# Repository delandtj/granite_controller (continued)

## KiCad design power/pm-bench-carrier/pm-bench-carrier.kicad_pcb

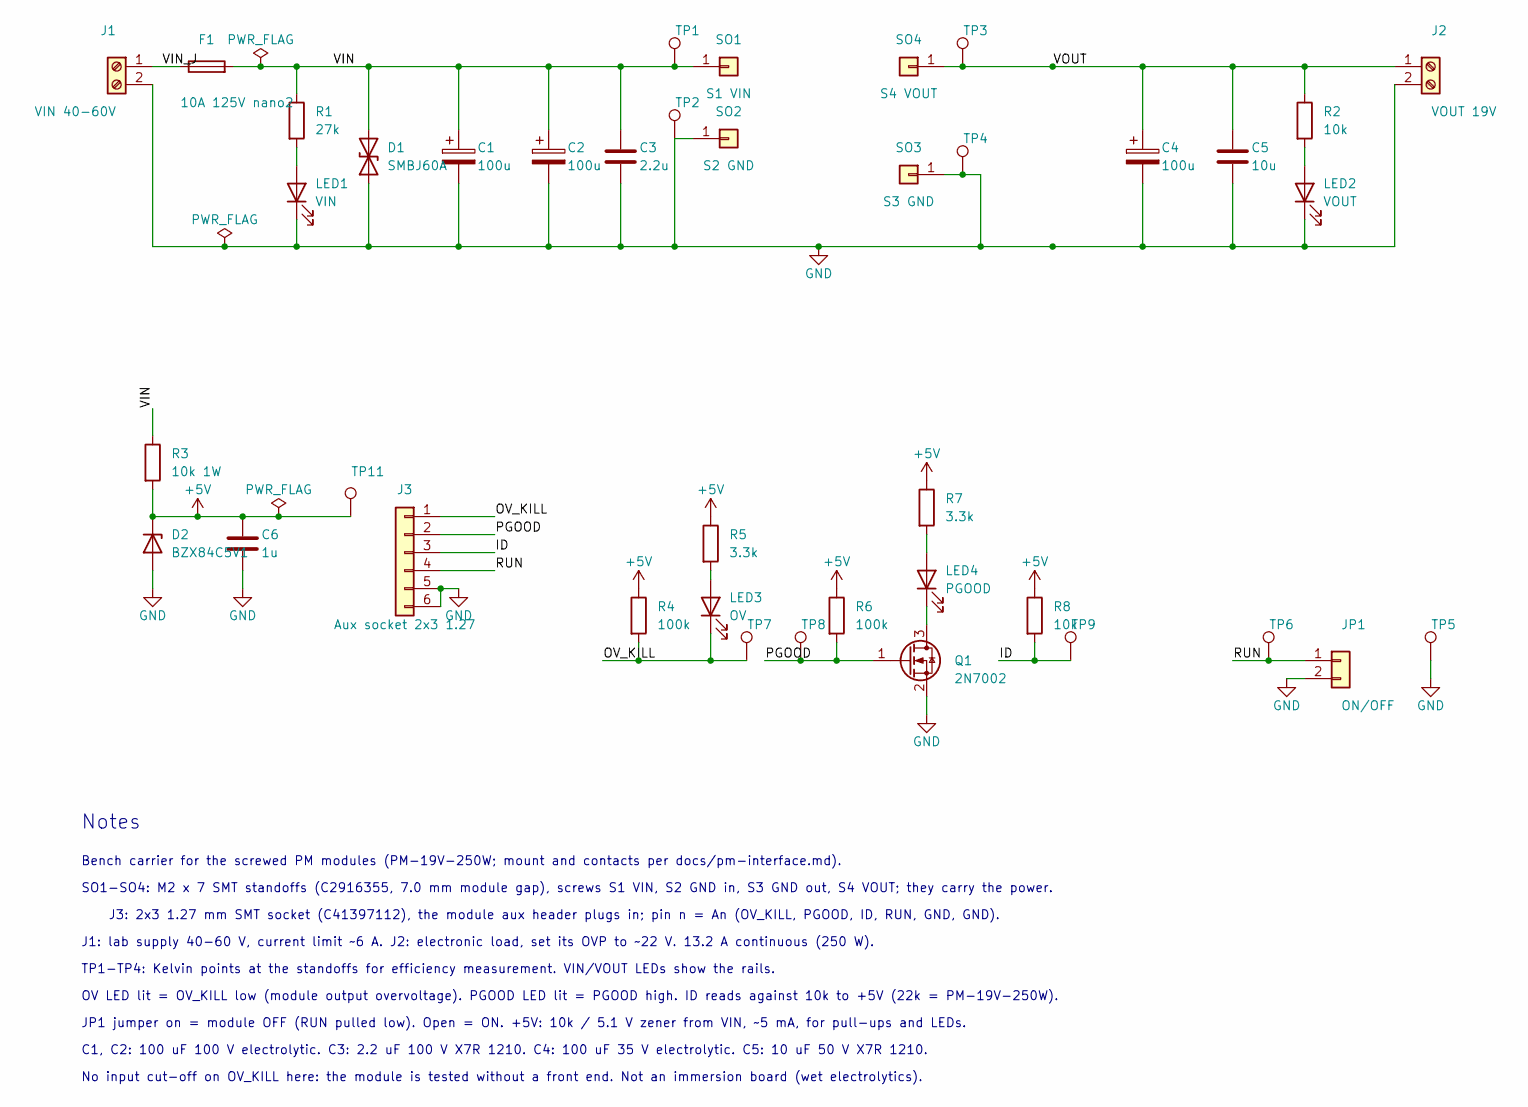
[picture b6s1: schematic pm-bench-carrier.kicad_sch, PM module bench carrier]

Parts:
C1, C2: 100u; CP_Radial_D10.0mm_P5.00mm
C3: 2.2u; C_1210_3225Metric; LCSC C55151
C4: 100u; CP_Radial_D8.0mm_P3.50mm
C5: 10u; C_1210_3225Metric; LCSC C2918502
C6: 1u; C_0603_1608Metric; LCSC C15849
D1: SMBJ60A; D_SMB; LCSC C353345
D2: BZX84C5V1; SOT-23; LCSC C27131
F1: 10A 125V nano2; Fuse_Littelfuse-NANO2-451_453; LCSC C44479
J1: VIN 40-60V; TerminalBlock_Phoenix_MKDS-3-2-5.08_1x02_P5.08mm_Horizontal
J2: VOUT 19V; TerminalBlock_Phoenix_MKDS-3-2-5.08_1x02_P5.08mm_Horizontal
J3: Aux socket 2x3 1.27; PM_Aux_Socket_2x03_P1.27; LCSC C41397112
JP1: ON/OFF; PinHeader_1x02_P2.54mm_Vertical
LED1: VIN; LED_0805_2012Metric; LCSC C2297
LED2: VOUT; LED_0805_2012Metric; LCSC C2297
LED3: OV; LED_0805_2012Metric; LCSC C84256
LED4: PGOOD; LED_0805_2012Metric; LCSC C2297
Q1: 2N7002; SOT-23; LCSC C8545
R1: 27k; R_1206_3216Metric; LCSC C17943
R2: 10k; R_0805_2012Metric; LCSC C17414
R3: 10k 1W; R_2512_6332Metric; LCSC C270956
R4, R6: 100k; R_0603_1608Metric; LCSC C25803
R5, R7: 3.3k; R_0603_1608Metric; LCSC C22978
R8: 10k; R_0603_1608Metric; LCSC C25804
SO1: S1 VIN; PM_Standoff_M2x7_SMTSO; LCSC C2916355
SO2: S2 GND; PM_Standoff_M2x7_SMTSO; LCSC C2916355
SO3: S3 GND; PM_Standoff_M2x7_SMTSO; LCSC C2916355
SO4: S4 VOUT; PM_Standoff_M2x7_SMTSO; LCSC C2916355
TP1: VIN_K; TestPoint_Loop_D2.50mm_Drill1.0mm
TP2: GNDIN_K; TestPoint_Loop_D2.50mm_Drill1.0mm
TP3: VOUT_K; TestPoint_Loop_D2.50mm_Drill1.0mm
TP4: GNDOUT_K; TestPoint_Loop_D2.50mm_Drill1.0mm
TP5: GND; TestPoint_Loop_D2.50mm_Drill1.0mm
TP6: RUN; TestPoint_Loop_D2.50mm_Drill1.0mm
TP7: OV_KILL; TestPoint_Loop_D2.50mm_Drill1.0mm
TP8: PGOOD; TestPoint_Loop_D2.50mm_Drill1.0mm
TP9: ID; TestPoint_Loop_D2.50mm_Drill1.0mm
TP11: +5V; TestPoint_Loop_D2.50mm_Drill1.0mm

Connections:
+5V: C6.1, D2.1 (K), R3.2, R4.1, R5.1, R6.1, R7.1, R8.1, TP11.1
/ID: J3.3, R8.2, TP9.1
/OV_KILL: J3.1, LED3.1 (K), R4.2, TP7.1
/PGOOD: J3.2, Q1.1 (G), R6.2, TP8.1
/RUN: J3.4, JP1.1, TP6.1
/VIN: C1.1, C2.1, C3.1, D1.2 (A2), F1.2, R1.1, R3.1, SO1.1, TP1.1
/VIN_J: F1.1, J1.1
/VOUT: C4.1, C5.1, J2.1, R2.1, SO4.1, TP3.1
GND: C1.2, C2.2, C3.2, C4.2, C5.2, C6.2, D1.1 (A1), D2.2 (A), J1.2, J2.2, J3.5, J3.6, JP1.2, LED1.1 (K), LED2.1 (K), Q1.2 (S), SO2.1, SO3.1, TP2.1, TP4.1, TP5.1
unnamed: LED1.2 (A), R1.2
unnamed: LED2.2 (A), R2.2
unnamed: LED3.2 (A), R5.2
unnamed: LED4.2 (A), R7.2
unnamed: LED4.1 (K), Q1.3 (D)

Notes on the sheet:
Notes
Bench carrier for the screwed PM modules (PM-19V-250W; mount and contacts per docs/pm-interface.md).
SO1-SO4: M2 x 7 SMT standoffs (C2916355, 7.0 mm module gap), screws S1 VIN, S2 GND in, S3 GND out, S4 VOUT; they carry the power.
J3: 2x3 1.27 mm SMT socket (C41397112), the module aux header plugs in; pin n = An (OV_KILL, PGOOD, ID, RUN, GND, GND).
J1: lab supply 40-60 V, current limit ~6 A. J2: electronic load, set its OVP to ~22 V. 13.2 A continuous (250 W).
TP1-TP4: Kelvin points at the standoffs for efficiency measurement. VIN/VOUT LEDs show the rails.
OV LED lit = OV_KILL low (module output overvoltage). PGOOD LED lit = PGOOD high. ID reads against 10k to +5V (22k = PM-19V-250W).
JP1 jumper on = module OFF (RUN pulled low). Open = ON. +5V: 10k / 5.1 V zener from VIN, ~5 mA, for pull-ups and LEDs.
C1, C2: 100 uF 100 V electrolytic. C3: 2.2 uF 100 V X7R 1210. C4: 100 uF 35 V electrolytic. C5: 10 uF 50 V X7R 1210.
No input cut-off on OV_KILL here: the module is tested without a front end. Not an immersion board (wet electrolytics).

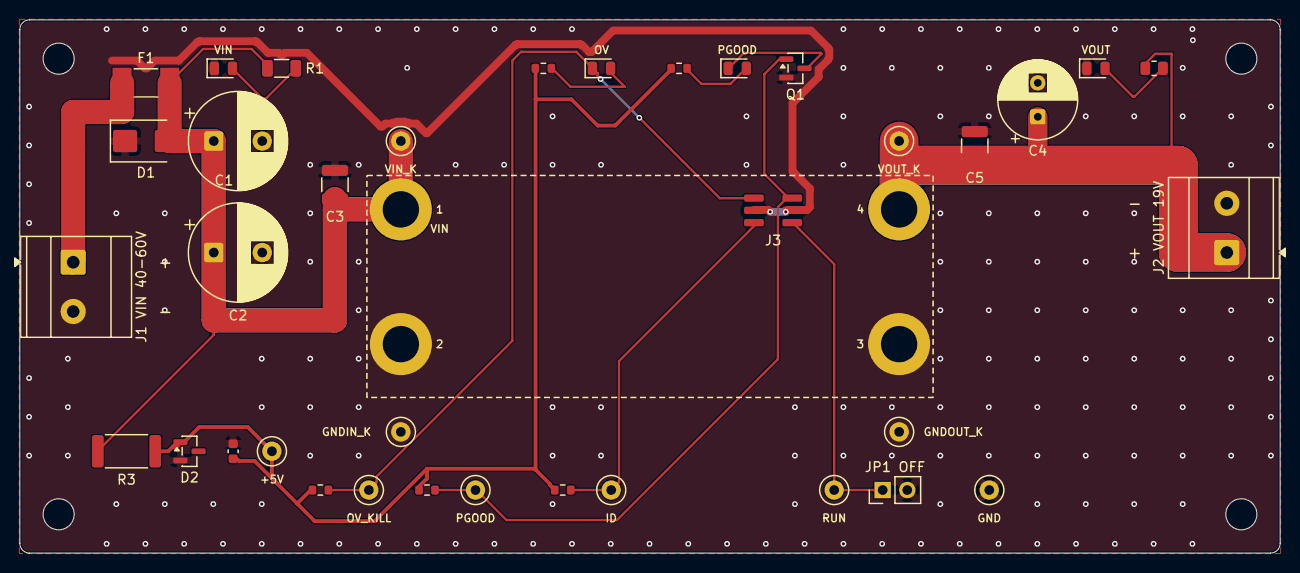
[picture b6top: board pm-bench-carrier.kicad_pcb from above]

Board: 2 copper layers, 130.0 x 55.0 mm, 45 parts (0 on the bottom side), 14 nets.

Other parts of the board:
H1, H2, H3, H4: MountingHole_3.2mm_M3
MOD1: PM_Module_Outline

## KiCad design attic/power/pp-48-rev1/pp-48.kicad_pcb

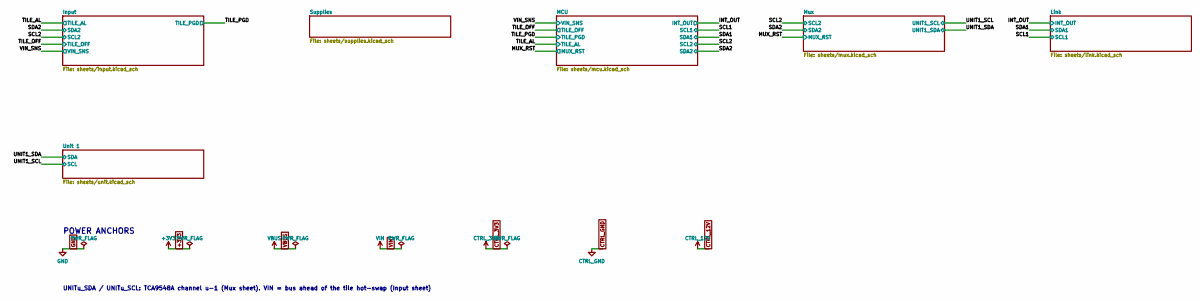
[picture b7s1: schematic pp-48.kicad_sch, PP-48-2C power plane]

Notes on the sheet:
POWER ANCHORS
UNITu_SDA / UNITu_SCL: TCA9548A channel u-1 (Mux sheet). VIN = bus ahead of the tile hot-swap (Input sheet)

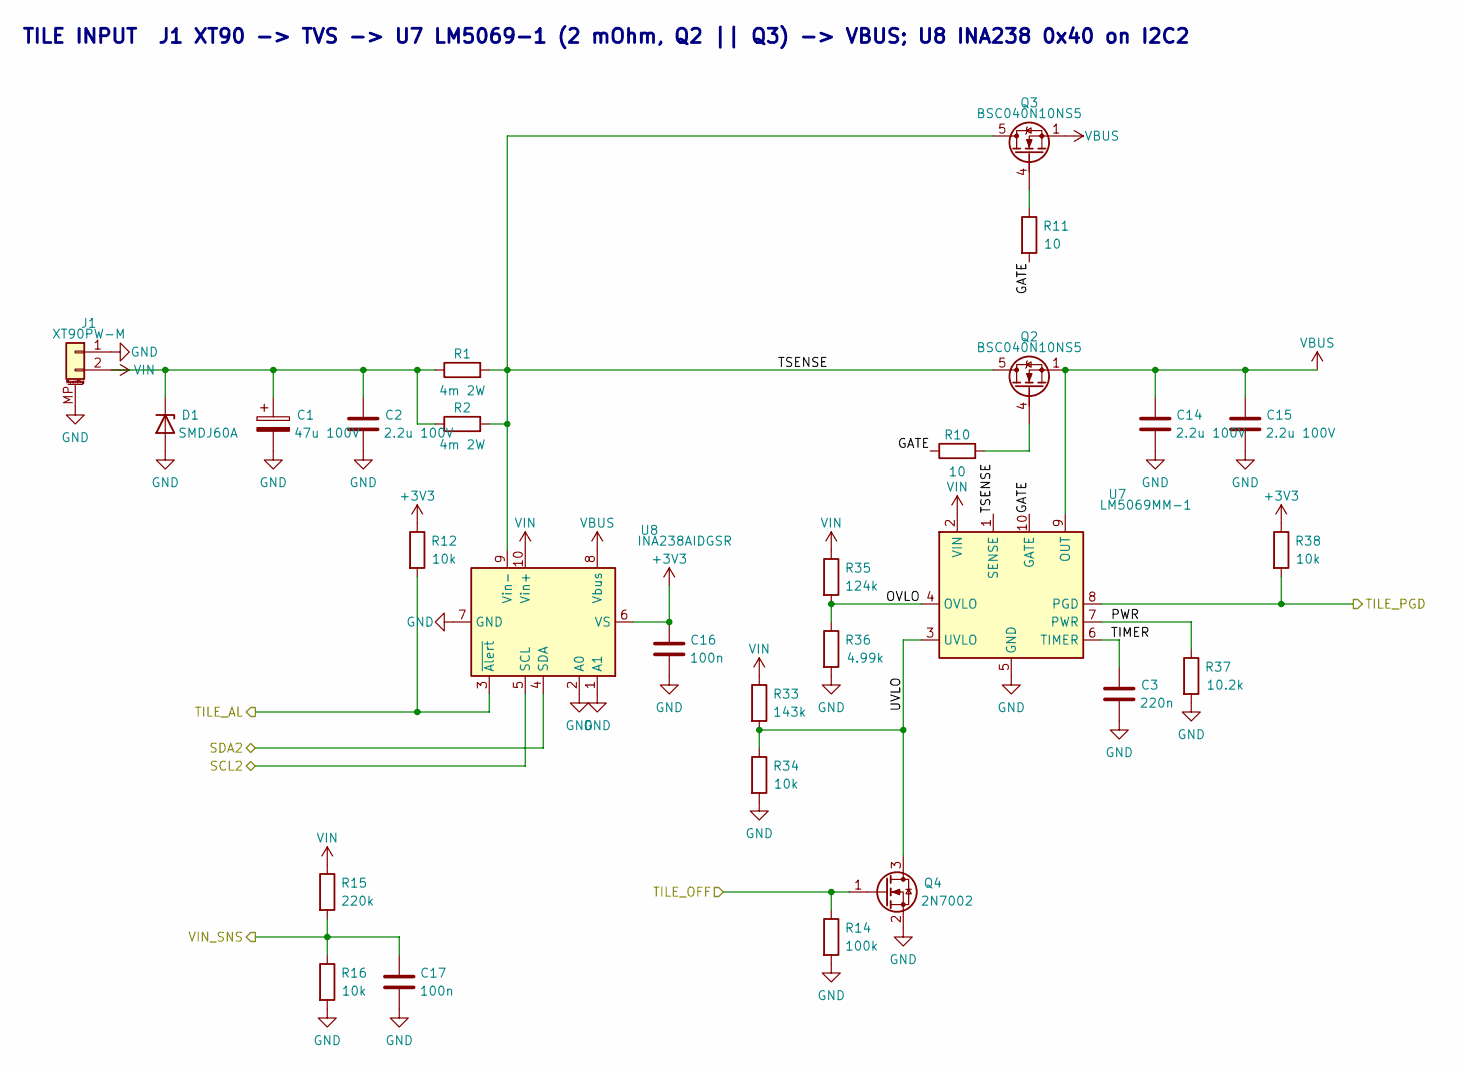
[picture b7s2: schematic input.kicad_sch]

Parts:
C1: 47u 100V; CP_Elec_10x10
C2, C14, C15: 2.2u 100V; C_1210_3225Metric; LCSC C338133
C3: 220n; C_0603_1608Metric
C16, C17: 100n; C_0402_1005Metric; LCSC C1525
D1: SMDJ60A; D_SMC
J1: XT90PW-M; AMASS_XT90PW-M_1x02_P10.90mm_Horizontal; MPN Amass XT90PW-M
Q2, Q3: BSC040N10NS5; TDSON-8-1; LCSC C534334
Q4: 2N7002; SOT-23; LCSC C8545
R1, R2: 4m 2W; R_2512_6332Metric
R10, R11: 10; R_0402_1005Metric
R12, R16, R34, R38: 10k; R_0402_1005Metric; LCSC C25744
R14: 100k; R_0402_1005Metric; LCSC C25741
R15: 220k; R_0805_2012Metric
R33: 143k; R_0805_2012Metric
R35: 124k; R_0805_2012Metric
R36: 4.99k; R_0402_1005Metric
R37: 10.2k; R_0402_1005Metric
U7: LM5069MM-1; MSOP-10_3x3mm_P0.5mm; LCSC C486026
U8: INA238AIDGSR; TSSOP-10_3x3mm_P0.5mm

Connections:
+3V3: C16.1, R12.1, R38.1, U8.6 (VS); also elsewhere on the board
/Input/GATE: R10.1, R11.2, U7.10 (GATE)
/Input/OVLO: R35.2, R36.1, U7.4 (OVLO)
/Input/PWR: R37.1, U7.7 (PWR)
/Input/TIMER: C3.1, U7.6 (TIMER)
/Input/TSENSE: Q2.5 (D), Q3.5 (D), R1.2, R2.2, U7.1 (SENSE), U8.9 (Vin-)
/Input/UVLO: Q4.3 (D), R33.2, R34.1, U7.3 (UVLO)
/SCL2: U8.5 (SCL); also elsewhere on the board
/SDA2: U8.4 (SDA); also elsewhere on the board
/TILE_AL: R12.2, U8.3 (~Alert); also elsewhere on the board
/TILE_OFF: Q4.1 (G), R14.1; also elsewhere on the board
/TILE_PGD: R38.2, U7.8 (PGD); also elsewhere on the board
/VIN_SNS: C17.1, R15.2, R16.1; also elsewhere on the board
GND: C1.2, C2.2, C3.2, C14.2, C15.2, C16.2, C17.2, D1.2 (A), J1.1, J1.MP (MountPin), Q4.2 (S), R14.2, R16.2, R34.2, R36.2, R37.2, U7.5 (GND), U8.1 (A1), U8.2 (A0), U8.7 (GND); also elsewhere on the board
unnamed: Q2.4 (G), R10.2
unnamed: Q3.4 (G), R11.1
VBUS: C14.1, C15.1, Q2.1 (S), Q2.2 (S), Q2.3 (S), Q3.1 (S), Q3.2 (S), Q3.3 (S), U7.9 (OUT), U8.8 (Vbus); also elsewhere on the board
VIN: C1.1, C2.1, D1.1 (K), J1.2, R1.1, R2.1, R15.1, R33.1, R35.1, U7.2 (VIN), U8.10 (Vin+); also elsewhere on the board

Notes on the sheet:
TILE INPUT J1 XT90 -> TVS -> U7 LM5069-1 (2 mOhm, Q2 || Q3) -> VBUS; U8 INA238 0x40 on I2C2

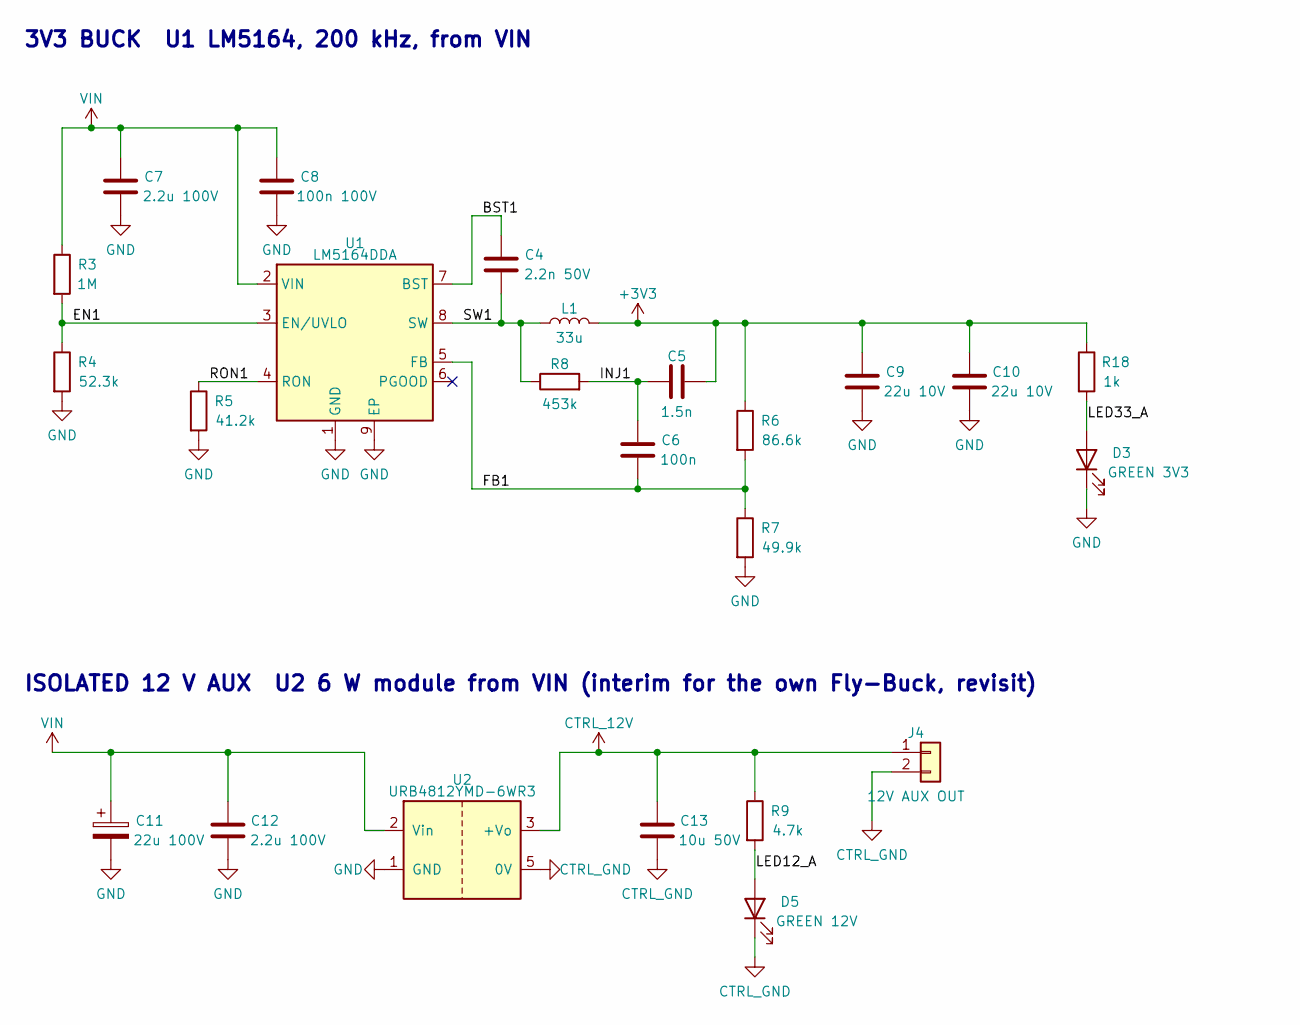
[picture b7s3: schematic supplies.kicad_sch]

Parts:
C4: 2.2n 50V; C_0402_1005Metric
C5: 1.5n; C_0402_1005Metric
C6: 100n; C_0402_1005Metric; LCSC C1525
C7, C12: 2.2u 100V; C_1210_3225Metric; LCSC C338133
C8: 100n 100V; C_0603_1608Metric
C9, C10: 22u 10V; C_1210_3225Metric
C11: 22u 100V; CP_Elec_10x10
C13: 10u 50V; C_1210_3225Metric
D3: GREEN 3V3; LED_0603_1608Metric; LCSC C2297
D5: GREEN 12V; LED_0603_1608Metric; LCSC C2297
J4: 12V AUX OUT; JST_PH_B2B-PH-K_1x02_P2.00mm_Vertical; LCSC C131337
L1: 33u; L_12x12mm_H6mm; MPN Bourns SRR1260-330M; LCSC C840528
R3: 1M; R_0805_2012Metric
R4: 52.3k; R_0402_1005Metric
R5: 41.2k; R_0402_1005Metric
R6: 86.6k; R_0402_1005Metric
R7: 49.9k; R_0402_1005Metric
R8: 453k; R_0402_1005Metric
R9: 4.7k; R_0603_1608Metric
R18: 1k; R_0402_1005Metric; LCSC C11702
U1: LM5164DDA; HSOP-8-1EP_3.9x4.9mm_P1.27mm_EP2.41x3.1mm; LCSC C477928
U2: URB4812YMD-6WR3; Converter_DCDC_1x1in_THT; MPN URB4812YMD-6WR3 (Mornsun pin-out; LCSC 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; LCSC C5369743

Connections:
+3V3: C5.2, C9.1, C10.1, L1.2, R6.1, R18.1; also elsewhere on the board
/Supplies/BST1: C4.1, U1.7 (BST)
/Supplies/EN1: R3.2, R4.1, U1.3 (EN/UVLO)
/Supplies/FB1: C6.2, R6.2, R7.1, U1.5 (FB)
/Supplies/INJ1: C5.1, C6.1, R8.2
/Supplies/LED12_A: D5.2 (A), R9.2
/Supplies/LED33_A: D3.2 (A), R18.2
/Supplies/RON1: R5.1, U1.4 (RON)
/Supplies/SW1: C4.2, L1.1, R8.1, U1.8 (SW)
CTRL_12V: C13.1, J4.1, R9.1, U2.3 (+Vo)
CTRL_GND: C13.2, D5.1 (K), J4.2, U2.5 (0V); also elsewhere on the board
GND: C7.2, C8.2, C9.2, C10.2, C11.2, C12.2, D3.1 (K), R4.2, R5.2, R7.2, U1.1 (GND), U1.9 (EP), U2.1 (GND); also elsewhere on the board
VIN: C7.1, C8.1, C11.1, C12.1, R3.1, U1.2 (VIN), U2.2 (Vin); also elsewhere on the board

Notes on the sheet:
3V3 BUCK U1 LM5164, 200 kHz, from VIN
ISOLATED 12 V AUX U2 6 W module from VIN (interim for the own Fly-Buck, revisit)

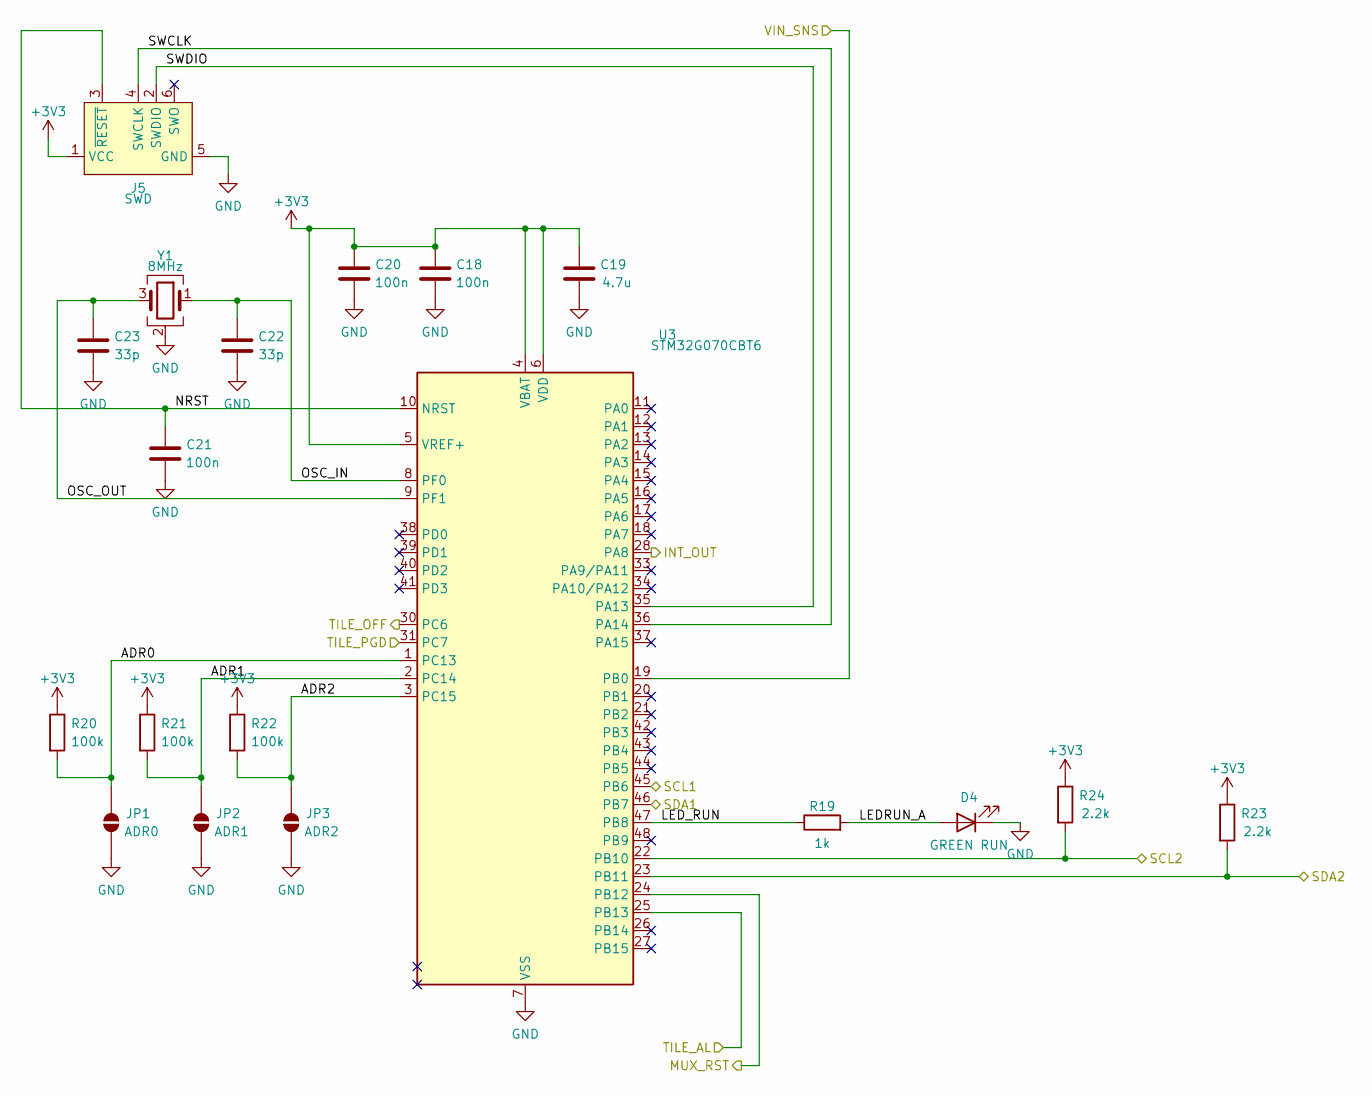
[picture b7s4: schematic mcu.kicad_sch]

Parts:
C18, C20, C21: 100n; C_0402_1005Metric; LCSC C1525
C19: 4.7u; C_0603_1608Metric
C22, C23: 33p; C_0402_1005Metric
D4: GREEN RUN; LED_0603_1608Metric; LCSC C2297
J5: SWD; Tag-Connect_TC2030-IDC-NL_2x03_P1.27mm_Vertical
JP1: ADR0; SolderJumper-2_P1.3mm_Open_RoundedPad1.0x1.5mm
JP2: ADR1; SolderJumper-2_P1.3mm_Open_RoundedPad1.0x1.5mm
JP3: ADR2; SolderJumper-2_P1.3mm_Open_RoundedPad1.0x1.5mm
R19: 1k; R_0402_1005Metric; LCSC C11702
R20, R21, R22: 100k; R_0402_1005Metric; LCSC C25741
R23, R24: 2.2k; R_0402_1005Metric; LCSC C25879
U3: STM32G070CBT6; LQFP-48_7x7mm_P0.5mm; LCSC C529338
Y1: 8MHz; Crystal_SMD_3225-4Pin_3.2x2.5mm; LCSC C7424755

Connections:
+3V3: C18.1, C19.1, C20.1, J5.1 (VCC), R20.1, R21.1, R22.1, R23.1, R24.1, U3.4 (VBAT), U3.5 (VREF+), U3.6 (VDD); also elsewhere on the board
/INT_OUT: U3.28 (PA8); also elsewhere on the board
/MCU/ADR0: JP1.1 (A), R20.2, U3.1 (PC13)
/MCU/ADR1: JP2.1 (A), R21.2, U3.2 (PC14)
/MCU/ADR2: JP3.1 (A), R22.2, U3.3 (PC15)
/MCU/LEDRUN_A: D4.2 (A), R19.2
/MCU/LED_RUN: R19.1, U3.47 (PB8)
/MCU/NRST: C21.1, J5.3 (~RESET), U3.10 (NRST)
/MCU/OSC_IN: C22.1, U3.8 (PF0), Y1.1
/MCU/OSC_OUT: C23.1, U3.9 (PF1), Y1.3
/MCU/SWCLK: J5.4 (SWCLK), U3.36 (PA14)
/MCU/SWDIO: J5.2 (SWDIO), U3.35 (PA13)
/MUX_RST: U3.24 (PB12); also elsewhere on the board
/SCL1: U3.45 (PB6); also elsewhere on the board
/SCL2: R24.2, U3.22 (PB10); also elsewhere on the board
/SDA1: U3.46 (PB7); also elsewhere on the board
/SDA2: R23.2, U3.23 (PB11); also elsewhere on the board
/TILE_AL: U3.25 (PB13); also elsewhere on the board
/TILE_OFF: U3.30 (PC6); also elsewhere on the board
/TILE_PGD: U3.31 (PC7); also elsewhere on the board
/VIN_SNS: U3.19 (PB0); also elsewhere on the board
GND: C18.2, C19.2, C20.2, C21.2, C22.2, C23.2, D4.1 (K), J5.5 (GND), JP1.2 (B), JP2.2 (B), JP3.2 (B), U3.7 (VSS), Y1.2 (G), Y1.4 (G); also elsewhere on the board

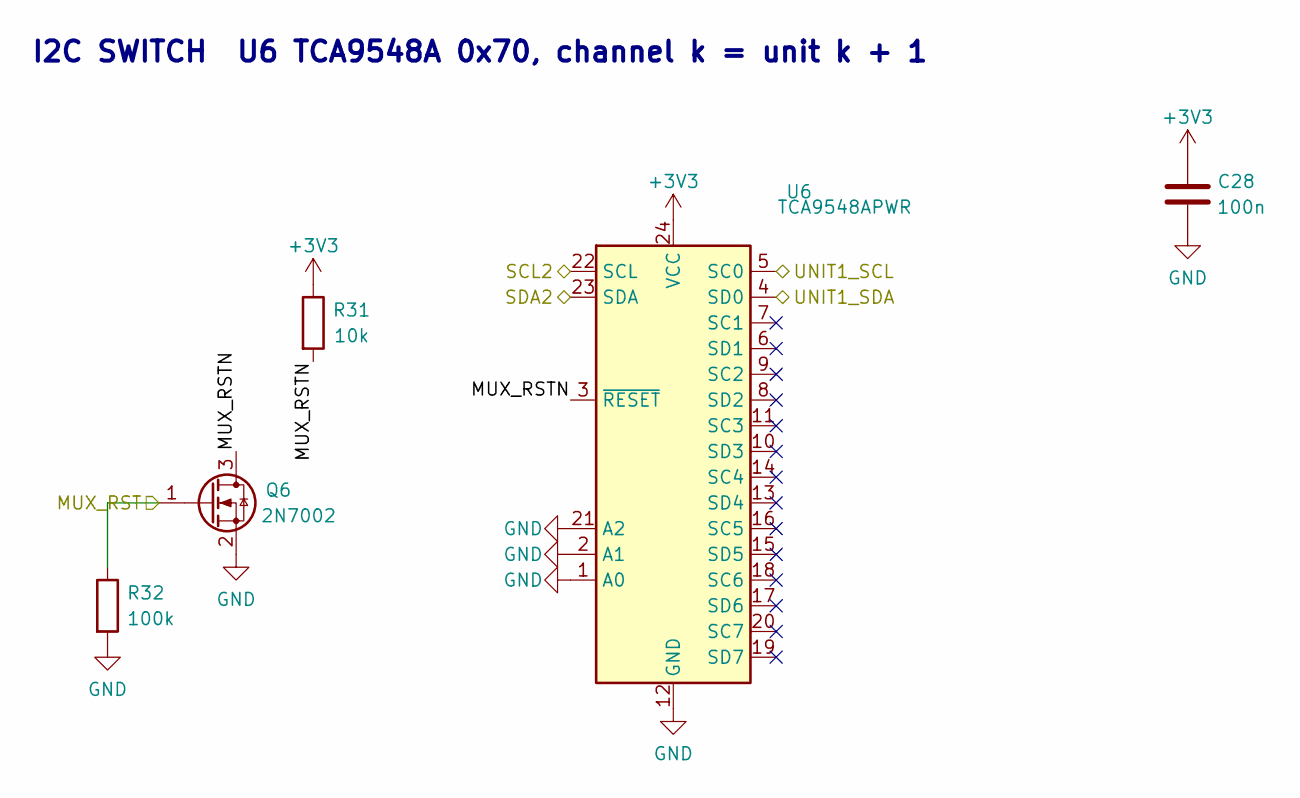
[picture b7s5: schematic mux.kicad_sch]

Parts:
C28: 100n; C_0402_1005Metric; LCSC C1525
Q6: 2N7002; SOT-23; LCSC C8545
R31: 10k; R_0402_1005Metric; LCSC C25744
R32: 100k; R_0402_1005Metric; LCSC C25741
U6: TCA9548APWR; TSSOP-24_4.4x7.8mm_P0.65mm; LCSC C130026

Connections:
+3V3: C28.1, R31.1, U6.24 (VCC); also elsewhere on the board
/MUX_RST: Q6.1 (G), R32.1; also elsewhere on the board
/Mux/MUX_RSTN: Q6.3 (D), R31.2, U6.3 (~RESET)
/SCL2: U6.22 (SCL); also elsewhere on the board
/SDA2: U6.23 (SDA); also elsewhere on the board
/UNIT1_SCL: U6.5 (SC0); also elsewhere on the board
/UNIT1_SDA: U6.4 (SD0); also elsewhere on the board
GND: C28.2, Q6.2 (S), R32.2, U6.1 (A0), U6.2 (A1), U6.12 (GND), U6.21 (A2); also elsewhere on the board

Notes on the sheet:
I2C SWITCH U6 TCA9548A 0x70, channel k = unit k + 1

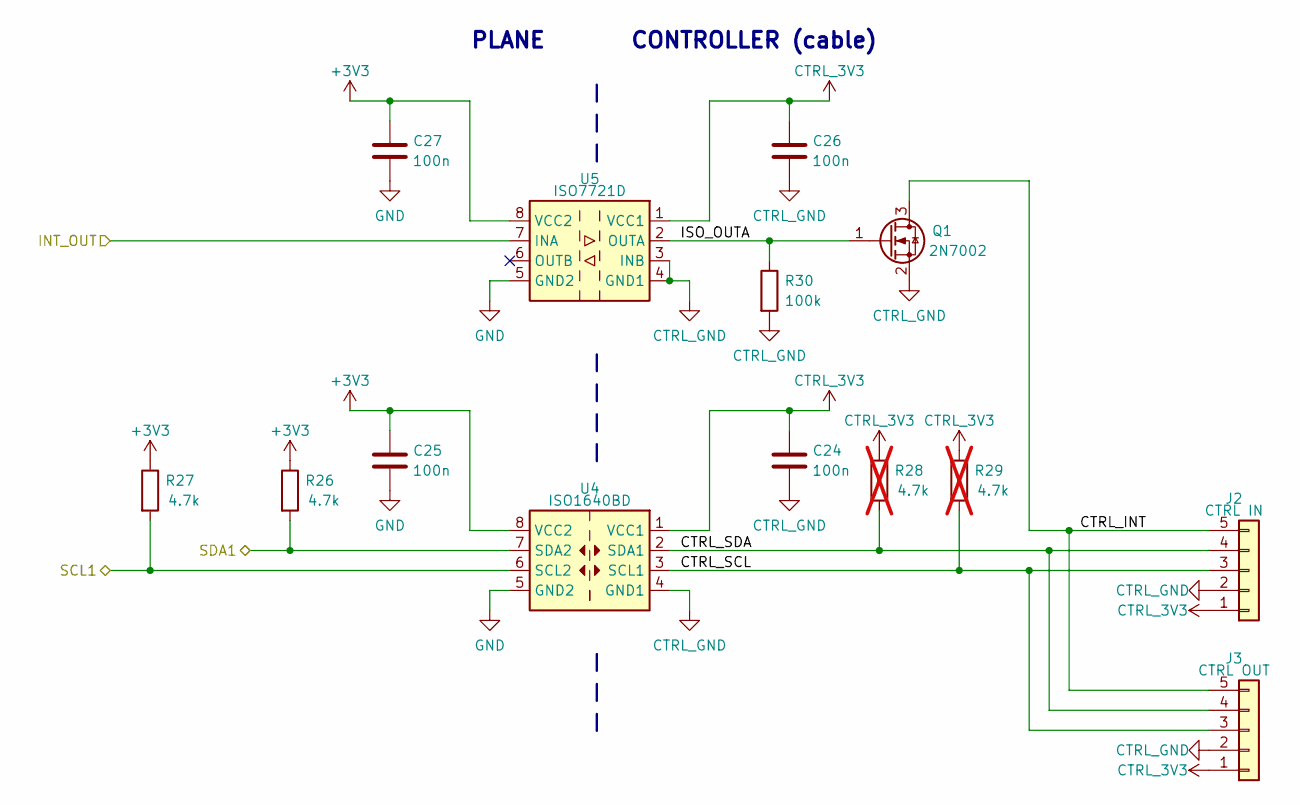
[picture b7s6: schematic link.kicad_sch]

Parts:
C24, C25, C26, C27: 100n; C_0402_1005Metric; LCSC C1525
J2: CTRL IN; JST_PH_B5B-PH-K_1x05_P2.00mm_Vertical; LCSC C157993
J3: CTRL OUT; JST_PH_B5B-PH-K_1x05_P2.00mm_Vertical; LCSC C157993
Q1: 2N7002; SOT-23; LCSC C8545
R26, R27: 4.7k; R_0402_1005Metric; LCSC C25900
R28, R29: 4.7k; R_0402_1005Metric; LCSC C25900; not fitted
R30: 100k; R_0402_1005Metric; LCSC C25741
U4: ISO1640BD; SOIC-8_3.9x4.9mm_P1.27mm; LCSC C5122339
U5: ISO7721D; SOIC-8_3.9x4.9mm_P1.27mm; LCSC C366164

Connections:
+3V3: C25.1, C27.1, R26.1, R27.1, U4.8 (VCC2), U5.8 (VCC2); also elsewhere on the board
/INT_OUT: U5.7 (INA); also elsewhere on the board
/Link/CTRL_INT: J2.5, J3.5, Q1.3 (D)
/Link/CTRL_SCL: J2.3, J3.3, R29.2, U4.3 (SCL1)
/Link/CTRL_SDA: J2.4, J3.4, R28.2, U4.2 (SDA1)
/Link/ISO_OUTA: Q1.1 (G), R30.1, U5.2 (OUTA)
/SCL1: R27.2, U4.6 (SCL2); also elsewhere on the board
/SDA1: R26.2, U4.7 (SDA2); also elsewhere on the board
CTRL_3V3: C24.1, C26.1, J2.1, J3.1, R28.1, R29.1, U4.1 (VCC1), U5.1 (VCC1)
CTRL_GND: C24.2, C26.2, J2.2, J3.2, Q1.2 (S), R30.2, U4.4 (GND1), U5.3 (INB), U5.4 (GND1); also elsewhere on the board
GND: C25.2, C27.2, U4.5 (GND2), U5.5 (GND2); also elsewhere on the board

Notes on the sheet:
PLANE
CONTROLLER (cable)

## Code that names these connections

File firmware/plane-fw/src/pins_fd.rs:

//! Every pin of the PP-48 core-fd board, named by its net (the
//! `link-mcp` and `link-fdcan` builds).
//!
//! `firmware/plane-core-fd-pins.toml` is generated from the schematic
//! generator (power/pp-48-fd/tools/sch/blocks/mcu.py) and is the truth
//! for this board: `build.rs` parses it and the [`core_pins!`] table
//! below and fails the build when a net moved to another port or
//! changed mode. Nothing else in the firmware may name a `P..`
//! peripheral: it takes the fields of [`CoreBoard`], so a pin
//! reassignment is one line here plus whatever the compiler then
//! complains about.
//!
//! One table for both CAN builds, because it is one board: the
//! MCP2518FD is fitted on the G070 build and not on the G0B1 build
//! (hardware ADR 0006 decision 6), and the difference is which fields
//! of [`CoreBoard`] the link module takes. The two builds hold opposite
//! halves of it:
//!
//! - `link-mcp` takes MCP_CS / SPI_SCK / SPI_MISO / SPI_MOSI / MCP_INT
//!   and leaves CAN_RX and CAN_TX untouched. That is not tidiness: the
//!   MCP2518FD's TXCAN drives the same ISO1044 TXD line as PB9, so PB9
//!   **must** stay in its reset state (analog, high-Z). Because the
//!   peripheral singletons are moved, not copied, a build that forgot
//!   and drove PB9 would have to say so in this file.
//! - `link-fdcan` takes CAN_RX and CAN_TX as FDCAN1_RX / FDCAN1_TX AF3
//!   and leaves the SPI pins and MCP_INT untouched (no MCP2518FD is
//!   fitted).
//!
//! PD2 (rev D's INT_OUT through the ISO7721) is free on this board:
//! EVENT frames replace the line (ADR 0005 decision 6), so it is not in
//! the generated map and not here.
//!
//! The type aliases carry the net's own name, in the net's own spelling
//! (`EXP_RSTN`, not `ExpRstn`), which is why the non-camel-case lint is
//! off for them: a pin map that does not read like the schematic is a
//! pin map nobody checks.

use embassy_stm32::Peri;
use embassy_stm32::peripherals;

/// Declare the board's nets: `NET : PORT = "mode";`.
///
/// `build.rs` reads the rows out of this file as text and checks them
/// against `firmware/plane-core-fd-pins.toml` (same port, same mode
/// string, and no net of the TOML that is neither listed here nor one
/// of the fixed debug / crystal / reset pins). The expansion is one
/// type alias per net, so `split` below cannot hand a net the wrong
/// port without a type error.
macro_rules! core_pins {
    ($( $(#[$doc:meta])* $net:ident : $port:ident = $mode:literal ; )*) => {
        $(
            $(#[$doc])*
            #[allow(non_camel_case_types)]
            pub type $net = peripherals::$port;
        )*
    };
}

core_pins! {
    /// ISO1044 RXD: the MCP2518FD's RXCAN hangs on the same net, so the
    /// G070 build leaves this pin in its reset state (analog) and only
    /// the G0B1 build drives it as FDCAN1_RX.
    CAN_RX : PB8 = "analog (G070) / FDCAN1_RX AF3 (G0B1)";
    /// ISO1044 TXD, driven by the MCP2518FD's TXCAN on the G070 build:
    /// that build must leave this pin analog and high-Z, or two drivers
    /// fight over the transceiver's input.
    CAN_TX : PB9 = "analog (G070) / FDCAN1_TX AF3 (G0B1)";

    /// MCP2518FD nCS, driven in software (the G0's SPI1 NSS output is
    /// not usable per transfer); 100k pull-up R33. G070 build.
    MCP_CS : PA4 = "output push-pull (SPI1_NSS by software)";
    /// SPI1 SCK to the MCP2518FD, at most 17 MHz at its 40 MHz SYSCLK.
    SPI_SCK : PA5 = "SPI1_SCK AF0";
    /// SPI1 MISO: the MCP2518FD's SDO.
    SPI_MISO : PA6 = "SPI1_MISO AF0";
    /// SPI1 MOSI: the MCP2518FD's SDI.
    SPI_MOSI : PA7 = "SPI1_MOSI AF0";
    /// MCP2518FD nINT, active low, 100k pull-up R34: an EXTI falling
    /// edge wakes the link task. G070 build.
    MCP_INT : PA0 = "input, EXTI falling";

    /// I2C2 SCL: the segment bus, TCA9548A 0x70 and one unit per
    /// channel.
    SCL2 : PA11 = "I2C2_SCL AF6";
    /// I2C2 SDA, same bus.
    SDA2 : PA12 = "I2C2_SDA AF6";
    /// High resets the mux and takes every channel off (Q6 inverts, so
    /// an MCU in reset leaves the mux running).
    MUX_RST : PB13 = "output push-pull";
    /// Low resets every unit's TCA6424A (bused, pull-ups on the units):
    /// CTRL 0x4D only.
    EXP_RSTN : PD0 = "output open-drain";

    /// Address straps, pulled up, DIP switch closed = 0; the plane's
    /// CAN node id is ADR\[2:0\] and its ADR 0003 address 0x30 + node.
    ADR0 : PA15 = "input";
    /// Address strap ADR1.
    ADR1 : PD1 = "input";
    /// Address strap ADR2.
    ADR2 : PA8 = "input";

    /// Core 48 V input through the 220k / 10k divider, ADC_IN15.
    VIN_SNS : PB11 = "ADC_IN15";
    /// Every edge retriggers the ~1 s press deadline monostable U301.
    /// Toggled only while a press runs (docs/press-deadline-line.md).
    PRESS_TRIG : PB12 = "output push-pull";
    /// Heartbeat LED, high = on.
    LED_RUN : PB14 = "output push-pull";
}

/// The core-fd board's pins, each in its net's type, plus the
/// peripherals behind them.
///
/// Built once by [`split`] from the peripheral singletons, then handed
/// out to the tasks. The link half differs per build and the rest does
/// not; a field a build does not take is a pin that stays in its reset
/// state, which for CAN_TX on the G070 build is a requirement and not
/// an accident (see the module docs).
pub struct CoreBoard {
    /// The segment bus peripheral (I2C2 master).
    pub i2c2: Peri<'static, peripherals::I2C2>,
    /// The ADC behind VIN_SNS.
    pub adc: Peri<'static, peripherals::ADC1>,
    /// The independent watchdog.
    pub iwdg: Peri<'static, peripherals::IWDG>,
    /// The flash controller, for the two CONFIG pages.
    pub flash: Peri<'static, peripherals::FLASH>,

    /// SPI1 to the MCP2518FD (`link-mcp`); no chip is fitted on the
    /// G0B1 build, so it stays here.
    #[cfg_attr(feature = "link-fdcan", allow(dead_code))]
    pub spi1: Peri<'static, peripherals::SPI1>,
    /// MCP2518FD nCS (`link-mcp`).
    #[cfg_attr(feature = "link-fdcan", allow(dead_code))]
    pub mcp_cs: Peri<'static, MCP_CS>,
    /// SPI1 SCK (`link-mcp`).
    #[cfg_attr(feature = "link-fdcan", allow(dead_code))]
    pub spi_sck: Peri<'static, SPI_SCK>,
    /// SPI1 MISO (`link-mcp`).
    #[cfg_attr(feature = "link-fdcan", allow(dead_code))]
    pub spi_miso: Peri<'static, SPI_MISO>,
    /// SPI1 MOSI (`link-mcp`).
    #[cfg_attr(feature = "link-fdcan", allow(dead_code))]
    pub spi_mosi: Peri<'static, SPI_MOSI>,
    /// MCP2518FD nINT (`link-mcp`).
    #[cfg_attr(feature = "link-fdcan", allow(dead_code))]
    pub mcp_int: Peri<'static, MCP_INT>,
    /// The EXTI line of MCP_INT, which is PA0's (`link-mcp`).
    #[cfg_attr(feature = "link-fdcan", allow(dead_code))]
    pub mcp_int_exti: Peri<'static, peripherals::EXTI0>,

    /// FDCAN1 (`link-fdcan`).
    #[cfg(feature = "link-fdcan")]
    pub fdcan1: Peri<'static, peripherals::FDCAN1>,
    /// ISO1044 RXD: FDCAN1_RX on the G0B1 build, untouched on the G070
    /// build. Held and not read there on purpose: see the module docs.
    #[cfg_attr(feature = "link-mcp", allow(dead_code))]
    pub can_rx: Peri<'static, CAN_RX>,
    /// ISO1044 TXD: FDCAN1_TX on the G0B1 build, untouched on the G070
    /// build, where the MCP2518FD's TXCAN drives the net and a second
    /// driver would fight it.
    #[cfg_attr(feature = "link-mcp", allow(dead_code))]
    pub can_tx: Peri<'static, CAN_TX>,

    /// I2C2 SCL (segment bus).
    pub scl2: Peri<'static, SCL2>,
    /// I2C2 SDA (segment bus).
    pub sda2: Peri<'static, SDA2>,
    /// MUX_RST.
    pub mux_rst: Peri<'static, MUX_RST>,
    /// EXP_RSTN.
    pub exp_rstn: Peri<'static, EXP_RSTN>,
    /// Address strap ADR0.
    pub adr0: Peri<'static, ADR0>,
    /// Address strap ADR1.
    pub adr1: Peri<'static, ADR1>,
    /// Address strap ADR2.
    pub adr2: Peri<'static, ADR2>,
    /// VIN_SNS.
    pub vin_sns: Peri<'static, VIN_SNS>,
    /// PRESS_TRIG.
    pub press_trig: Peri<'static, PRESS_TRIG>,
    /// LED_RUN.
    pub led_run: Peri<'static, LED_RUN>,
}

/// Name every pin of `p`.
///
/// Each assignment is checked against the alias above by the compiler,
/// and the alias against the generated pin map by `build.rs`.
pub fn split(p: embassy_stm32::Peripherals) -> CoreBoard {
    CoreBoard {
        i2c2: p.I2C2,
        adc: p.ADC1,
        iwdg: p.IWDG,
        flash: p.FLASH,
        spi1: p.SPI1,
        mcp_cs: p.PA4,
        spi_sck: p.PA5,
        spi_miso: p.PA6,
        spi_mosi: p.PA7,
        mcp_int: p.PA0,
        mcp_int_exti: p.EXTI0,
        #[cfg(feature = "link-fdcan")]
        fdcan1: p.FDCAN1,
        can_rx: p.PB8,
        can_tx: p.PB9,
        scl2: p.PA11,
        sda2: p.PA12,
        mux_rst: p.PB13,
        exp_rstn: p.PD0,
        adr0: p.PA15,
        adr1: p.PD1,
        adr2: p.PA8,
        vin_sns: p.PB11,
        press_trig: p.PB12,
        led_run: p.PB14,
    }
}

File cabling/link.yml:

# The controller's one cable to its plane. It carries the CAN FD link
# and the controller's only supply. Source: docs/adr/0006 decisions 3,
# 4, 8 and 9.
metadata:
  title: Controller link
  notes: >-
    A 6-way halogen-free IDC ribbon (3M HF365/06SF), female both ends,
    pin n to pin n, 0.30-0.35 m (controller on the carrier, core in the
    infra frame, pod layout 2026-11), 1 m at most. The controller end is keyed; the core end
    is a bare plug and is not, and a reversed cable puts 12 V on CANH /
    CANL (survived by both transceivers, the link stays down). The
    controller terminates its end of the bus. The other end is two
    jumper caps on JP301 of the last unit (1-2 and 3-4), none anywhere
    else.

connectors:
  CTRL:
    type: IDC socket 2x3, 2.54 mm
    subtype: to controller-fd J15 (keyed box header)
    pinlabels: [CANH, CANL, LINK_GND, LINK_GND, AUX_12V, AUX_12V]
    notes: the controller's only power input
  CORE:
    type: IDC socket 2x3, 2.54 mm
    subtype: to core J2 LINK IN (bare plug, not keyed)
    pinlabels: [CAN_P, CAN_N, LINK_GND, LINK_GND, AUX_12V, AUX_12V]
    notes: isolated from the 48 V bus at the core

cables:
  W_LINK:
    gauge: 28 AWG
    length: 0.35
    wirecount: 6
    color_code: IEC
    notes: flat ribbon, 1.27 mm pitch; about 2 W on AUX_12V

connections:
  - - CTRL: [1-6]
    - W_LINK: [1-6]
    - CORE: [1-6]

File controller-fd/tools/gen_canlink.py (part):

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
# ---------------------------------------------------------------- notes
text('CAN link (ADR 0006 decision 9): MCP2518FD CAN FD controller on the W5500 SPI bus (GPIO19 SCLK / GPIO20 MOSI / GPIO21 MISO), '
     'nCS GPIO2, nINT GPIO3; TCAN1044V transceiver, STB on GPIO0.', 20.32, 25.4)
text('Not isolated: the controller ground is LINK_GND (link pins 3 / 4); its 12 V is AUX_12V (pins 5 / 6), OR-ed from every core.', 20.32, 29.21)
text('MCP2518FD: SPI <= 17 MHz at SYSCLK 40 MHz (its own transactions; W5500 nCS GPIO18 stays). nINT push-pull after reset (IOCON.INTOD = 0), '
     '10k pull-up holds it high before init. GPIO0 / GPIO1 / CLKO unused; INT0 / INT1 have no pull-ups here: firmware sets them as outputs, low.', 20.32, 33.02)
text('Symbol: KiCad MCP2517FD-xSL (MCP2518FD is the pin-compatible successor, SOIC-14).', 20.32, 36.83)

# ---------------------------------------------------------------- MCP2518FD
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    'Description': 'CAN FD transceiver 8 Mbit/s, VIO, STB; TJA1049T-3 symbol (same pinout)',
    'MANUFACTURER': 'TI', 'MPN': 'TCAN1044VDRQ1', 'LCSC': 'C1852061'},
    stub=5.08, ref_off=(2.54, -12.7), val_off=(2.54, 12.7))
text('STB: GPIO0, internal pull-up to VIO = standby until firmware drives it low (normal mode).', 154.94, 121.92)
text('VCC +5V (BUCK_5V via the SS34 OR, ~5.0 V loaded; 4.5-5.5 V), VIO +3V3.', 154.94, 125.73)

cap('C60', '100n', 203.2, 68.58, P5V, GND, 'C1525', 'CL05B104KO5NNNC', 'Samsung')
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    '5': ('g', 'AUX_12V', 'output'), '6': ('g', 'AUX_12V', 'output'),
}, {'Footprint': 'Connector_IDC:IDC-Header_2x03_P2.54mm_Horizontal',
    'Datasheet': 'https://www.lcsc.com/datasheet/lcsc_datasheet_1810161728_BOOMELE-Boom-Precision-Elec-2-54-2-3P_C34945.pdf',
    'Description': 'Plane link, keyed 2x3 right-angle box header at the right edge (6-pin IDC ribbon to core 1): 1 CANH, 2 CANL, 3/4 LINK_GND, 5/6 AUX_12V',
    'MANUFACTURER': 'BOOMELE', 'MPN': '2.54-2*3P Bent Header', 'LCSC': 'C34945'},
    stub=7.62, ref_off=(0, -6.35), val_off=(0, 7.62))
text('J15: keyed 2x3 right-angle box header; pre-made 6-pin IDC ribbon to core 1 link plug (ADR 0006 decision 9).', 284.48, 76.2)
text('Ribbon pin n to plug pin n: 1 CANH, 2 CANL, 3 / 4 LINK_GND (= controller GND), 5 / 6 AUX_12V.', 284.48, 80.01)

# ESD at the header
part('Power_Protection:NUP2105L', 'D13', 'PESD2CANFD24V-TR', 287.02, 134.62, {
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
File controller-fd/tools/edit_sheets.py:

import re, uuid
def tops(t):
    """(start,end) of top-level blocks (one tab indent)."""
    res=[]
    for m in re.finditer(r'\n\t\((?=[a-z_])',t):
        p=m.start()+1; d=0
        for j in range(p,len(t)):
            if t[j]=='(':d+=1
            elif t[j]==')':
                d-=1
                if d==0: res.append((p,j+1)); break
    return res
def remove(t,pred):
    bl=[(a,b) for a,b in tops(t) if pred(t[a:b])]
    for a,b in reversed(bl):
        # also drop the preceding newline
        t=t[:a-1]+t[b:]
    return t,len(bl)
def is_sym_ref(refs):
    def f(b):
        if not b.startswith('\t(symbol'): return False
        m=re.search(r'\(property "Reference" "([^"]+)"',b)
        return m and m.group(1) in refs
    return f
def has_uuid(us):
    def f(b):
        m=re.search(r'\n\t\t\(uuid "([^"]+)"\)',b)
        return m and m.group(1) in us and not b.startswith('\t(symbol')
    return f

# ---- power sheet
p='schematic/power.kicad_sch'; t=open(p).read()
t,n=remove(t,is_sym_ref({'J11','J12','D11','#PWR1101','#PWR1102'})); print('power syms',n)
t,n=remove(t,has_uuid({'abd49673-1a47-4122-8701-a056294d64f7','6d182ba0-1da4-44d0-89de-4db95c0ac58a',
  '4f1358b9-a526-4bb2-91bf-0d62e89ad7f8','102bba19-4da9-4da8-9187-c444ef9dbee2','e4b01129-501d-44e1-9447-61db585d3067',
  'f6afddef-cff1-4ca5-a366-2a2abdb0ae94'})); print('power wires',n)
t,n=remove(t,lambda b: b.startswith('\t(label "12V_IN_B"') or (b.startswith('\t(label "VIN_12V"') and '(at 72.39 139.7' in b)); print('power labels',n)
# J11 wire now starts at the AUX_12V label
assert '(xy 25.4 114.3) (xy 59.69 114.3)' in t
t=t.replace('(xy 25.4 114.3) (xy 59.69 114.3)','(xy 30.48 114.3) (xy 59.69 114.3)')
# label 12V_IN_A -> global label AUX_12V
a,b=[(a,b) for a,b in tops(t) if t[a:b].startswith('\t(label "12V_IN_A"')][0]
u=re.search(r'\(uuid "([^"]+)"\)',t[a:b]).group(1)
gl=('\t(global_label "AUX_12V"\n\t\t(shape input)\n\t\t(at 30.48 114.3 180)\n\t\t(fields_autoplaced yes)\n'
    '\t\t(effects\n\t\t\t(font\n\t\t\t\t(size 1.27 1.27)\n\t\t\t)\n\t\t\t(justify right)\n\t\t)\n'
    '\t\t(uuid "%s")\n\t\t(property "Intersheetrefs" "${INTERSHEET_REFS}"\n\t\t\t(at 30.48 114.3 0)\n'
    '\t\t\t(effects\n\t\t\t\t(font\n\t\t\t\t\t(size 1.27 1.27)\n\t\t\t\t)\n\t\t\t\t(justify right)\n\t\t\t\t(hide yes)\n\t\t\t)\n\t\t)\n\t)')%u
t=t[:a]+gl+t[b:]
old='12 V input: two plane aux feeds (plane J4: PH 2p, 1 CTRL_12V, 2 CTRL_GND) -> one SS34 each (OR-ing + reverse polarity) -> SMAJ15A -> LMR51430 buck (1.1 MHz) -> 5.2 V. No fuse: the plane iso module limits its own output.'
assert old in t
t=t.replace(old,'12 V input: AUX_12V from the plane link box header J15 pins 5 / 6 (OR-ed from every core, ADR 0006 decision 4) -> SS34 D10 (reverse polarity) -> SMAJ15A -> LMR51430 buck (1.1 MHz) -> 5.44 V (BUCK_5V). No fuse: the cores\' iso modules limit their own output. GND = LINK_GND.')
t=t.replace('(title "Granite controller rev D - ','(title "Granite controller FD - ')
open(p,'w').write(t)

# ---- MCU sheet
p='schematic/mcu.kicad_sch'; t=open(p).read()
for old,new,shape in (('EXP_INT','CAN_STB','output'),('PLANE_SDA','CAN_nCS','output'),('PLANE_SCL','CAN_nINT','input')):
    a,b=[(a,b) for a,b in tops(t) if t[a:b].startswith('\t(global_label "%s"'%old)][0]
    blk=t[a:b].replace('(global_label "%s"'%old,'(global_label "%s"'%new).replace('(shape bidirectional)','(shape %s)'%shape)
    t=t[:a]+blk+t[b:]
for old,new in (('Rev D: GPIO2/3 plane link (HP I2C), GPIO6/7 local I2C, GPIO10/11/4/15 dry inputs 1-4, GPIO0 EXP_INT',
                 'FD: GPIO2 / GPIO3 MCP2518FD nCS / nINT (CAN link, SPI shared with the W5500), GPIO0 TCAN1044V STB, GPIO6/7 local I2C, GPIO10/11/4/15 dry inputs 1-4'),
                ('Plane link pull-ups (2.2k) and EXP_INT 10k on the Plane link sheet.','CAN_nCS / CAN_nINT 10k pull-ups on the CAN link sheet.')):
    assert old in t, old; t=t.replace(old,new)
t=t.replace('(title "Granite controller rev D - ','(title "Granite controller FD - ')
open(p,'w').write(t)

# ---- root
p='granite-controller-fd.kicad_sch'; t=open(p).read()
t=t.replace('(property "Sheetname" "Plane link"','(property "Sheetname" "CAN link"').replace('"schematic/planelink.kicad_sch"','"schematic/canlink.kicad_sch"')
open(p,'w').write(t)
